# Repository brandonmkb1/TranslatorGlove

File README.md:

# TranslatorGlove
Glove that will be able to translate sign language to letters on an LCD Screen 

one file is an example of using capacitance touch sensors through digital pins. We would put 16 different specific positions on the glove to differentiate each letter.

another one is to measure resisitivity from flex sensors. It would be downloaded to an excel spread sheet to see the difference between all of them.
the python file is to acompany this

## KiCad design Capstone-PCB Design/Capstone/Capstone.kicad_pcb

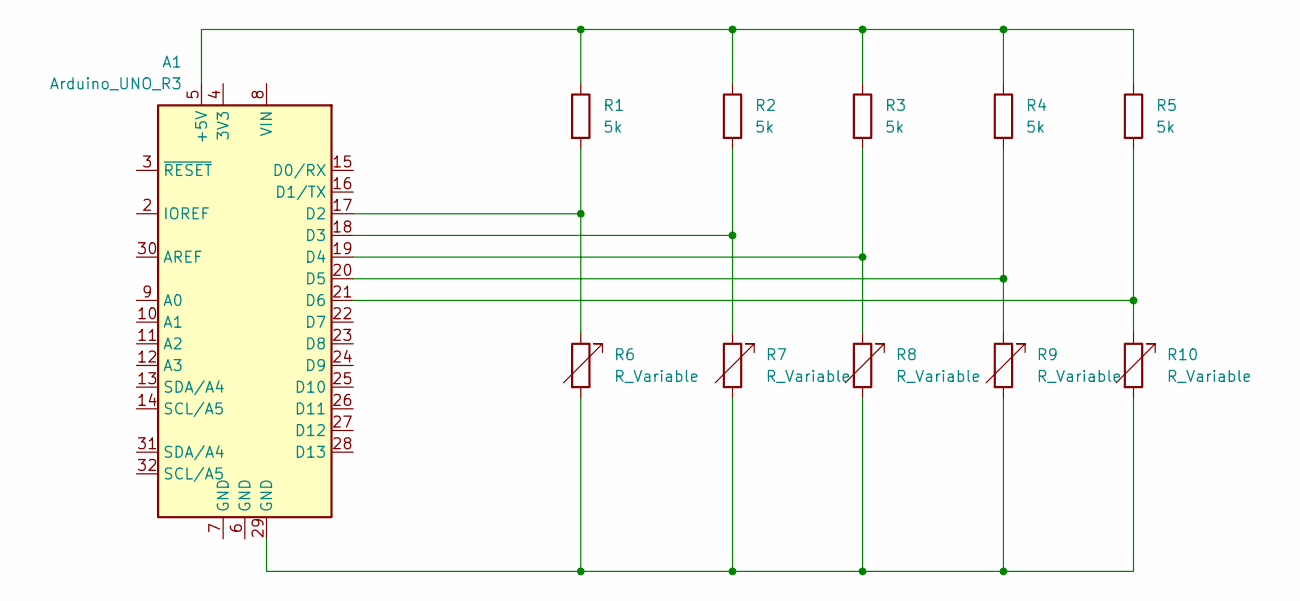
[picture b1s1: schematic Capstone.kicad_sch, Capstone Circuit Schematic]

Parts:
A1: Arduino_UNO_R3; Arduino_UNO_R3_WithMountingHoles
R1, R2, R3, R4, R5: 5k; R_Axial_DIN0207_L6.3mm_D2.5mm_P7.62mm_Horizontal
R6, R7, R8, R9, R10: R_Variable; SolderJumper-2_P1.3mm_Open_Pad1.0x1.5mm

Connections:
unnamed: A1.5 (+5V), R1.1, R2.1, R3.1, R4.1, R5.1
unnamed: A1.17 (D2), R1.2, R6.1
unnamed: A1.18 (D3), R2.2, R7.1
unnamed: A1.19 (D4), R3.2, R8.1
unnamed: A1.20 (D5), R4.2, R9.1
unnamed: A1.21 (D6), R5.2, R10.1
unnamed: A1.29 (GND), R6.2, R7.2, R8.2, R9.2, R10.2

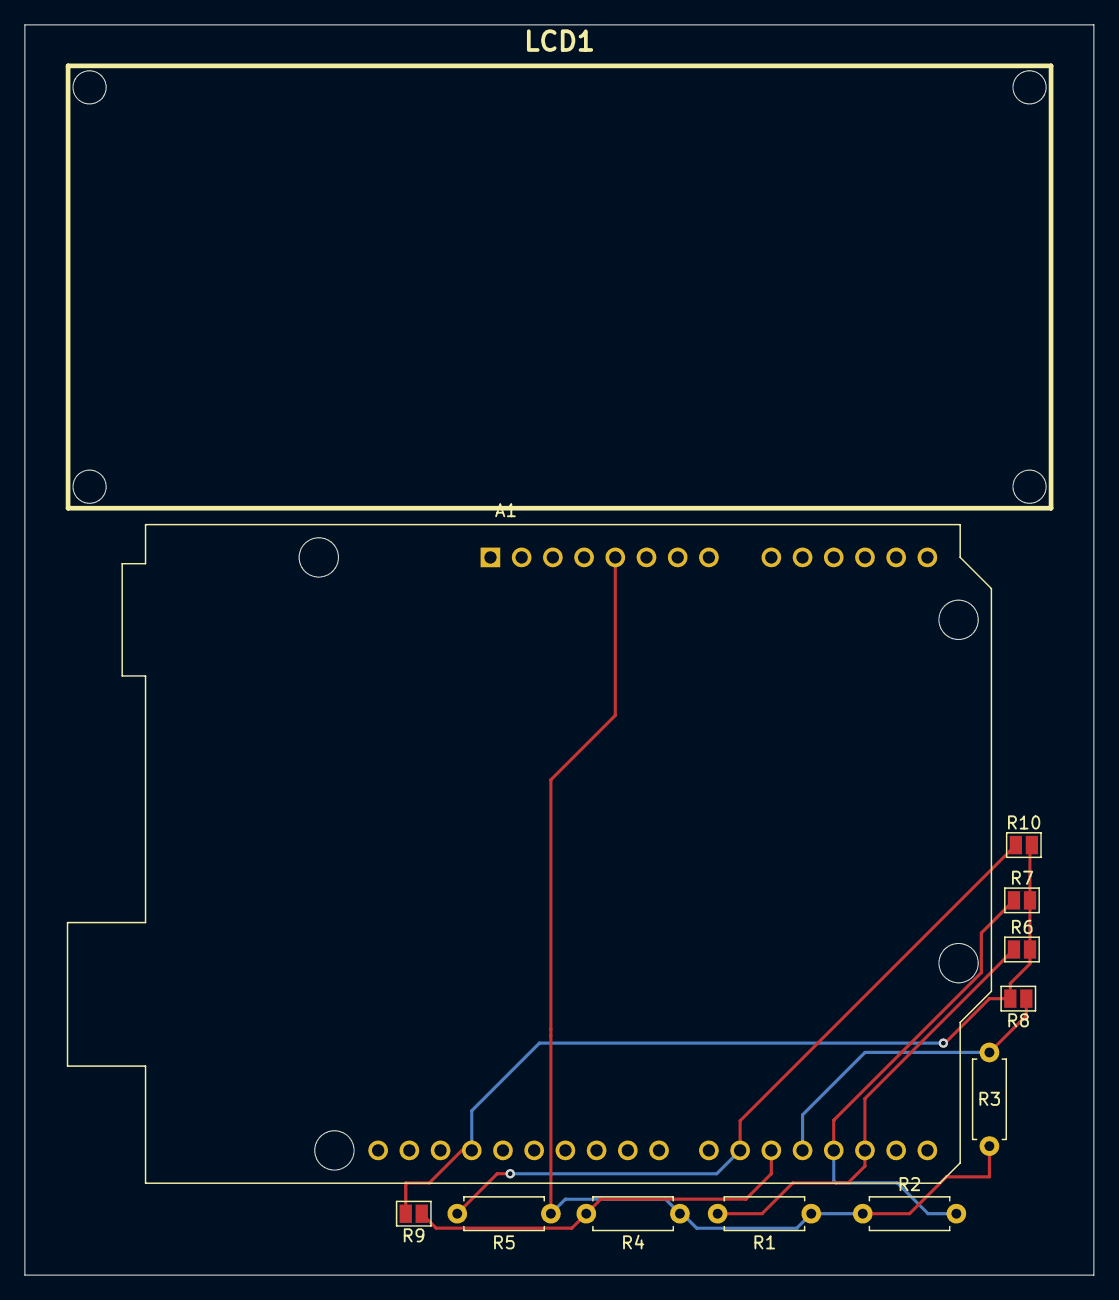
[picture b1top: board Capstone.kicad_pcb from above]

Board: 2 copper layers, 87.0 x 101.8 mm, 12 parts (0 on the bottom side), 7 nets.

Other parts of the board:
LCD1: LCD-16x2

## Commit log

2024-09-24 Create ReadResistivity.py
    reads resistivity and creates .csv files
2024-10-23 Create ASL.m
    MATLAB simulation to randomize values and obtain letters through the command window
2024-10-30 Created a folder with all the simulation tests
2024-10-30 created hardware test folder
2024-10-30 Capture 100 images for each letter
2024-10-30 Created dataset from captured photos
2024-10-30 Trained Machine Learning model
2024-10-30 Testing hand models
2024-10-31 Add files via upload
    PCB Design for KiCAD
2024-10-31 unzipped kicad folder
2024-10-31 I corrected Akrams name
2024-11-01 I added the LCD onto the schematic and its footprint design
2024-11-07 PCB Design simulated w/ no errors
